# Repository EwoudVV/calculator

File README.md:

# Calculator

a calculator built from logic chips. there is no microcontroller or firmware.

it takes whole numbers from 0 to 9999 and does addition, subtraction, multiplication and division. it shows negative results, rounds division to two decimal places, and has lights for overflow, divide by zero and a full input.

three registers hold the numbers. a shared decimal adder works through them one digit at a time. the controller runs the loops for multiplication and long division.

## calculation times

calculated at a 96 kHz clock.

| calculation | clock cycles | time |
| --- | ---: | ---: |
| 27 + 15 or 27 − 15 | 43 | 0.45 ms |
| 12 × 34 | 369 | 3.84 ms |
| 99 × 99 | 2,253 | 23.47 ms |
| 7 ÷ 2 | 373 | 3.89 ms |
| 9999 ÷ 1 | 709 | 7.39 ms |

## pcb

the board is 140 × 120 mm. the keypad and display are on the front, with surface mount logic on both sides. it runs on 5 V.

open [calculator.kicad_pro](calculator.kicad_pro) in KiCad 10. the [build notes](BUILD.md) have the board status and parts list. progress from the breadboard design is in [JOURNAL.md](JOURNAL.md).

made for Hack Club Half Life, week 5

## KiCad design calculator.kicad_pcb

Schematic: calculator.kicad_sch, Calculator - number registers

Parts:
C101, C102, C103, C104, C105, C106, C107, C108, C109, C110, C111, C112, C113, C114, C115, C121, C122: 100n; C_0603_1608Metric
J101: 5V / GND; PinHeader_1x02_P2.54mm_Vertical
U101, U102, U103, U104, U105, U106, U107, U108, U109, U110, U111, U112: CD74HC299M96; SOIC-20W_7.5x12.8mm_P1.27mm
U113, U114, U115: CD74HC157M96; SOIC-16_3.9x9.9mm_P1.27mm
U121, U122: CD74HC153M96; SOIC-16_3.9x9.9mm_P1.27mm

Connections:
+5V: C101.1, C102.1, C103.1, C104.1, C105.1, C106.1, C107.1, C108.1, C109.1, C110.1, C111.1, C112.1, C113.1, C114.1, C115.1, C121.1, C122.1, J101.1, U101.20 (VCC), U102.20 (VCC), U103.20 (VCC), U104.20 (VCC), U105.20 (VCC), U106.20 (VCC), U107.20 (VCC), U108.20 (VCC), U109.20 (VCC), U110.20 (VCC), U111.20 (VCC), U112.20 (VCC), U113.16 (VCC), U114.16 (VCC), U115.16 (VCC), U121.16 (VCC), U122.16 (VCC); also elsewhere on the board
/ALU_DIGIT_0: U113.3 (I1a), U114.3 (I1a), U115.3 (I1a); also elsewhere on the board
/ALU_DIGIT_1: U113.6 (I1b), U114.6 (I1b), U115.6 (I1b); also elsewhere on the board
/ALU_DIGIT_2: U113.10 (I1c), U114.10 (I1c), U115.10 (I1c); also elsewhere on the board
/ALU_DIGIT_3: U113.13 (I1d), U114.13 (I1d), U115.13 (I1d); also elsewhere on the board
/A_SERIAL_RIGHT_0: U101.11 (Ds0), U113.4 (Za)
/A_SERIAL_RIGHT_1: U102.11 (Ds0), U113.7 (Zb)
/A_SERIAL_RIGHT_2: U103.11 (Ds0), U113.9 (Zc)
/A_SERIAL_RIGHT_3: U104.11 (Ds0), U113.12 (Zd)
/A_TOP_0: U101.8 (Q0), U121.3 (I3a)
/A_TOP_1: U102.8 (Q0), U121.13 (I3b)
/A_TOP_2: U103.8 (Q0), U122.3 (I3a)
/A_TOP_3: U104.8 (Q0), U122.13 (I3b)
/A_UNITS_0: U101.17 (Q7), U113.2 (I0a); also elsewhere on the board
/A_UNITS_1: U102.17 (Q7), U113.5 (I0b); also elsewhere on the board
/A_UNITS_2: U103.17 (Q7), U113.11 (I0c); also elsewhere on the board
/A_UNITS_3: U104.17 (Q7), U113.14 (I0d); also elsewhere on the board
/BANK_RESET_N: U101.9 (Mr), U102.9 (Mr), U103.9 (Mr), U104.9 (Mr), U105.9 (Mr), U106.9 (Mr), U107.9 (Mr), U108.9 (Mr), U109.9 (Mr), U110.9 (Mr), U111.9 (Mr), U112.9 (Mr); also elsewhere on the board
/B_SERIAL_RIGHT_0: U105.11 (Ds0), U114.4 (Za)
/B_SERIAL_RIGHT_1: U106.11 (Ds0), U114.7 (Zb)
/B_SERIAL_RIGHT_2: U107.11 (Ds0), U114.9 (Zc)
/B_SERIAL_RIGHT_3: U108.11 (Ds0), U114.12 (Zd)
/B_TOP_0: U105.8 (Q0)
/B_TOP_1: U106.8 (Q0)
/B_TOP_2: U107.8 (Q0)
/B_TOP_3: U108.8 (Q0)
/B_UNITS_0: U105.17 (Q7), U114.2 (I0a); also elsewhere on the board
/B_UNITS_1: U106.17 (Q7), U114.5 (I0b); also elsewhere on the board
/B_UNITS_2: U107.17 (Q7), U114.11 (I0c); also elsewhere on the board
/B_UNITS_3: U108.17 (Q7), U114.14 (I0d); also elsewhere on the board
/LEFT_LOAD_0: U101.18 (Ds7), U105.18 (Ds7), U109.18 (Ds7), U121.7 (Za)
/LEFT_LOAD_1: U102.18 (Ds7), U106.18 (Ds7), U110.18 (Ds7), U121.9 (Zb)
/LEFT_LOAD_2: U103.18 (Ds7), U107.18 (Ds7), U111.18 (Ds7), U122.7 (Za)
/LEFT_LOAD_3: U104.18 (Ds7), U108.18 (Ds7), U112.18 (Ds7), U122.9 (Zb)
/W_SERIAL_RIGHT_0: U109.11 (Ds0), U115.4 (Za)
/W_SERIAL_RIGHT_1: U110.11 (Ds0), U115.7 (Zb)
/W_SERIAL_RIGHT_2: U111.11 (Ds0), U115.9 (Zc)
/W_SERIAL_RIGHT_3: U112.11 (Ds0), U115.12 (Zd)
/W_TOP_0: U109.8 (Q0)
/W_TOP_1: U110.8 (Q0)
/W_TOP_2: U111.8 (Q0)
/W_TOP_3: U112.8 (Q0)
/W_UNITS_0: U109.17 (Q7), U115.2 (I0a); also elsewhere on the board
/W_UNITS_1: U110.17 (Q7), U115.5 (I0b); also elsewhere on the board
/W_UNITS_2: U111.17 (Q7), U115.11 (I0c); also elsewhere on the board
/W_UNITS_3: U112.17 (Q7), U115.14 (I0d); also elsewhere on the board
A_ROTATE_RIGHT: U101.1 (S0), U102.1 (S0), U103.1 (S0), U104.1 (S0); also elsewhere on the board
A_SHIFT_LEFT: U101.19 (S1), U102.19 (S1), U103.19 (S1), U104.19 (S1); also elsewhere on the board
A_WRITE_ALU: U113.1 (S); also elsewhere on the board
BANK_CLK: U101.12 (Cp), U102.12 (Cp), U103.12 (Cp), U104.12 (Cp), U105.12 (Cp), U106.12 (Cp), U107.12 (Cp), U108.12 (Cp), U109.12 (Cp), U110.12 (Cp), U111.12 (Cp), U112.12 (Cp); also elsewhere on the board
B_ROTATE_RIGHT: U105.1 (S0), U106.1 (S0), U107.1 (S0), U108.1 (S0); also elsewhere on the board
B_SHIFT_LEFT: U105.19 (S1), U106.19 (S1), U107.19 (S1), U108.19 (S1); also elsewhere on the board
B_WRITE_ALU: U114.1 (S); also elsewhere on the board
GND: C101.2, C102.2, C103.2, C104.2, C105.2, C106.2, C107.2, C108.2, C109.2, C110.2, C111.2, C112.2, C113.2, C114.2, C115.2, C121.2, C122.2, J101.2, U101.2 (OE1), U101.3 (OE2), U101.10 (GND), U102.2 (OE1), U102.3 (OE2), U102.10 (GND), U103.2 (OE1), U103.3 (OE2), U103.10 (GND), U104.2 (OE1), U104.3 (OE2), U104.10 (GND), U105.2 (OE1), U105.3 (OE2), U105.10 (GND), U106.2 (OE1), U106.3 (OE2), U106.10 (GND), U107.2 (OE1), U107.3 (OE2), U107.10 (GND), U108.2 (OE1), U108.3 (OE2), U108.10 (GND), U109.2 (OE1), U109.3 (OE2), U109.10 (GND), U110.2 (OE1), U110.3 (OE2), U110.10 (GND), U111.2 (OE1), U111.3 (OE2), U111.10 (GND), U112.2 (OE1), U112.3 (OE2), U112.10 (GND), U113.8 (GND), U113.15 (E), U114.8 (GND), U114.15 (E), U115.8 (GND), U115.15 (E), U121.1 (Ea), U121.6 (I0a), U121.8 (GND), U121.10 (I0b), U121.15 (Eb), U122.1 (Ea), U122.6 (I0a), U122.8 (GND), U122.10 (I0b), U122.15 (Eb); also elsewhere on the board
KEY_DIGIT_0: U121.5 (I1a); also elsewhere on the board
KEY_DIGIT_1: U121.11 (I1b); also elsewhere on the board
KEY_DIGIT_2: U122.5 (I1a); also elsewhere on the board
KEY_DIGIT_3: U122.11 (I1b); also elsewhere on the board
LEFT_SELECT_0: U121.14 (S0), U122.14 (S0); also elsewhere on the board
LEFT_SELECT_1: U121.2 (S1), U122.2 (S1); also elsewhere on the board
QUOTIENT_DIGIT_0: U121.4 (I2a); also elsewhere on the board
QUOTIENT_DIGIT_1: U121.12 (I2b); also elsewhere on the board
QUOTIENT_DIGIT_2: U122.4 (I2a); also elsewhere on the board
QUOTIENT_DIGIT_3: U122.12 (I2b); also elsewhere on the board
W_ROTATE_RIGHT: U109.1 (S0), U110.1 (S0), U111.1 (S0), U112.1 (S0); also elsewhere on the board
W_SHIFT_LEFT: U109.19 (S1), U110.19 (S1), U111.19 (S1), U112.19 (S1); also elsewhere on the board
W_WRITE_ALU: U115.1 (S); also elsewhere on the board

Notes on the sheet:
A: first number
BCD bit 0
BCD bit 1
BCD bit 2
BCD bit 3
B: second number
W: working/result number
Shared digit for a left shift
Number registers. Shared arithmetic is on sheet 2.
S0,S1: 00 hold / 10 arithmetic rotate / 01 append a digit.
Unused parallel ports are outputs with OE1/OE2 LOW; no external load.
Parallel-load mode 11 must never be selected.

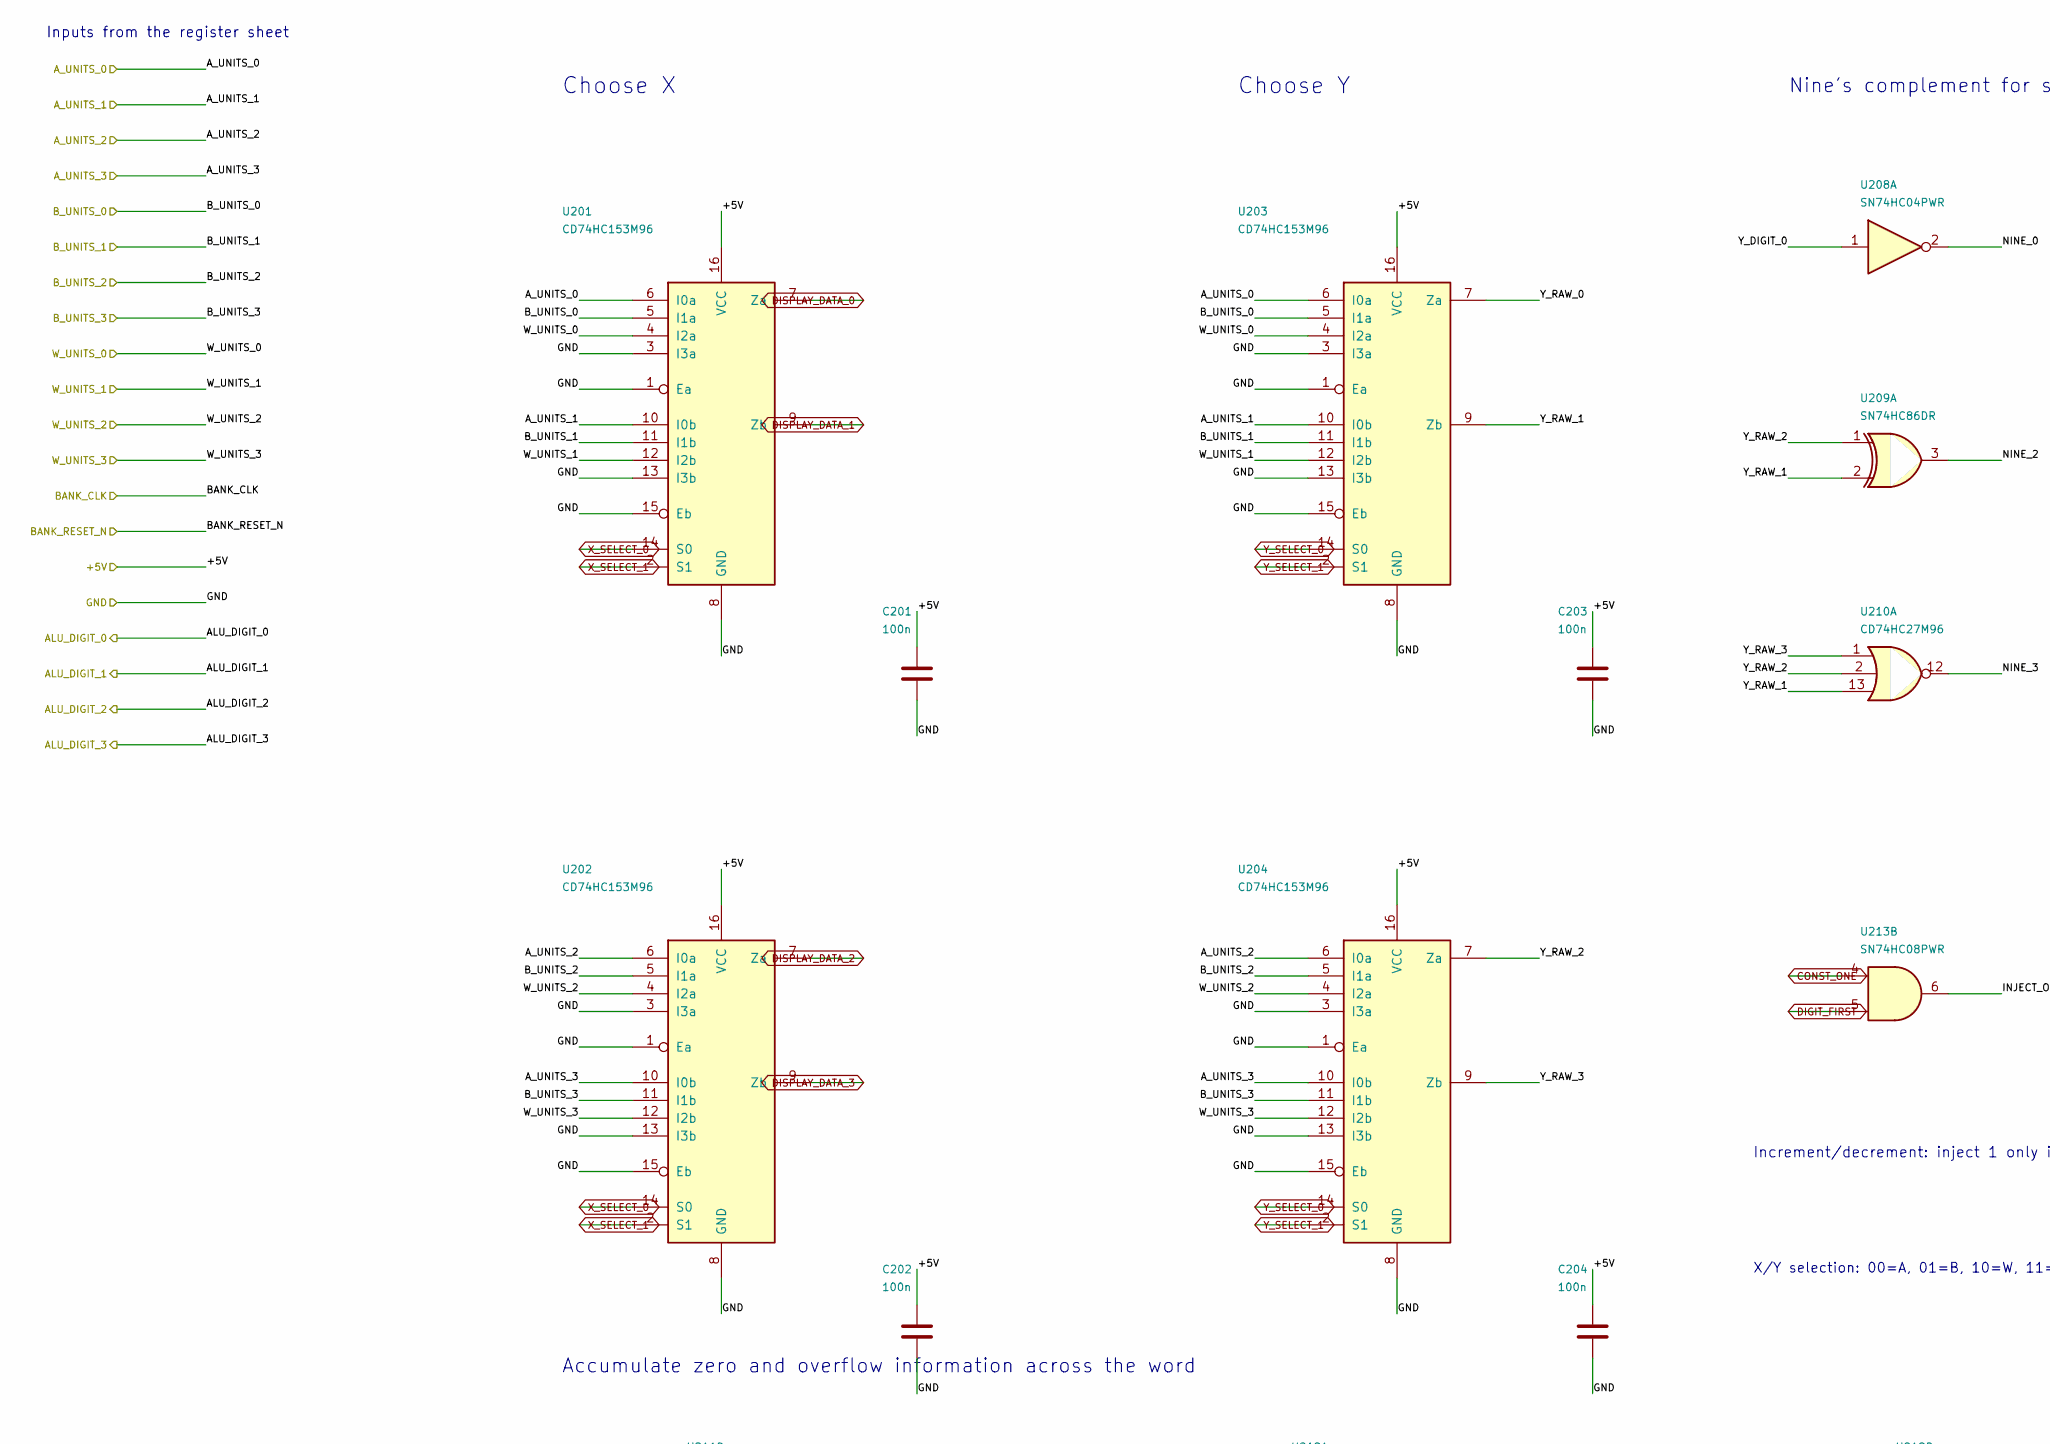
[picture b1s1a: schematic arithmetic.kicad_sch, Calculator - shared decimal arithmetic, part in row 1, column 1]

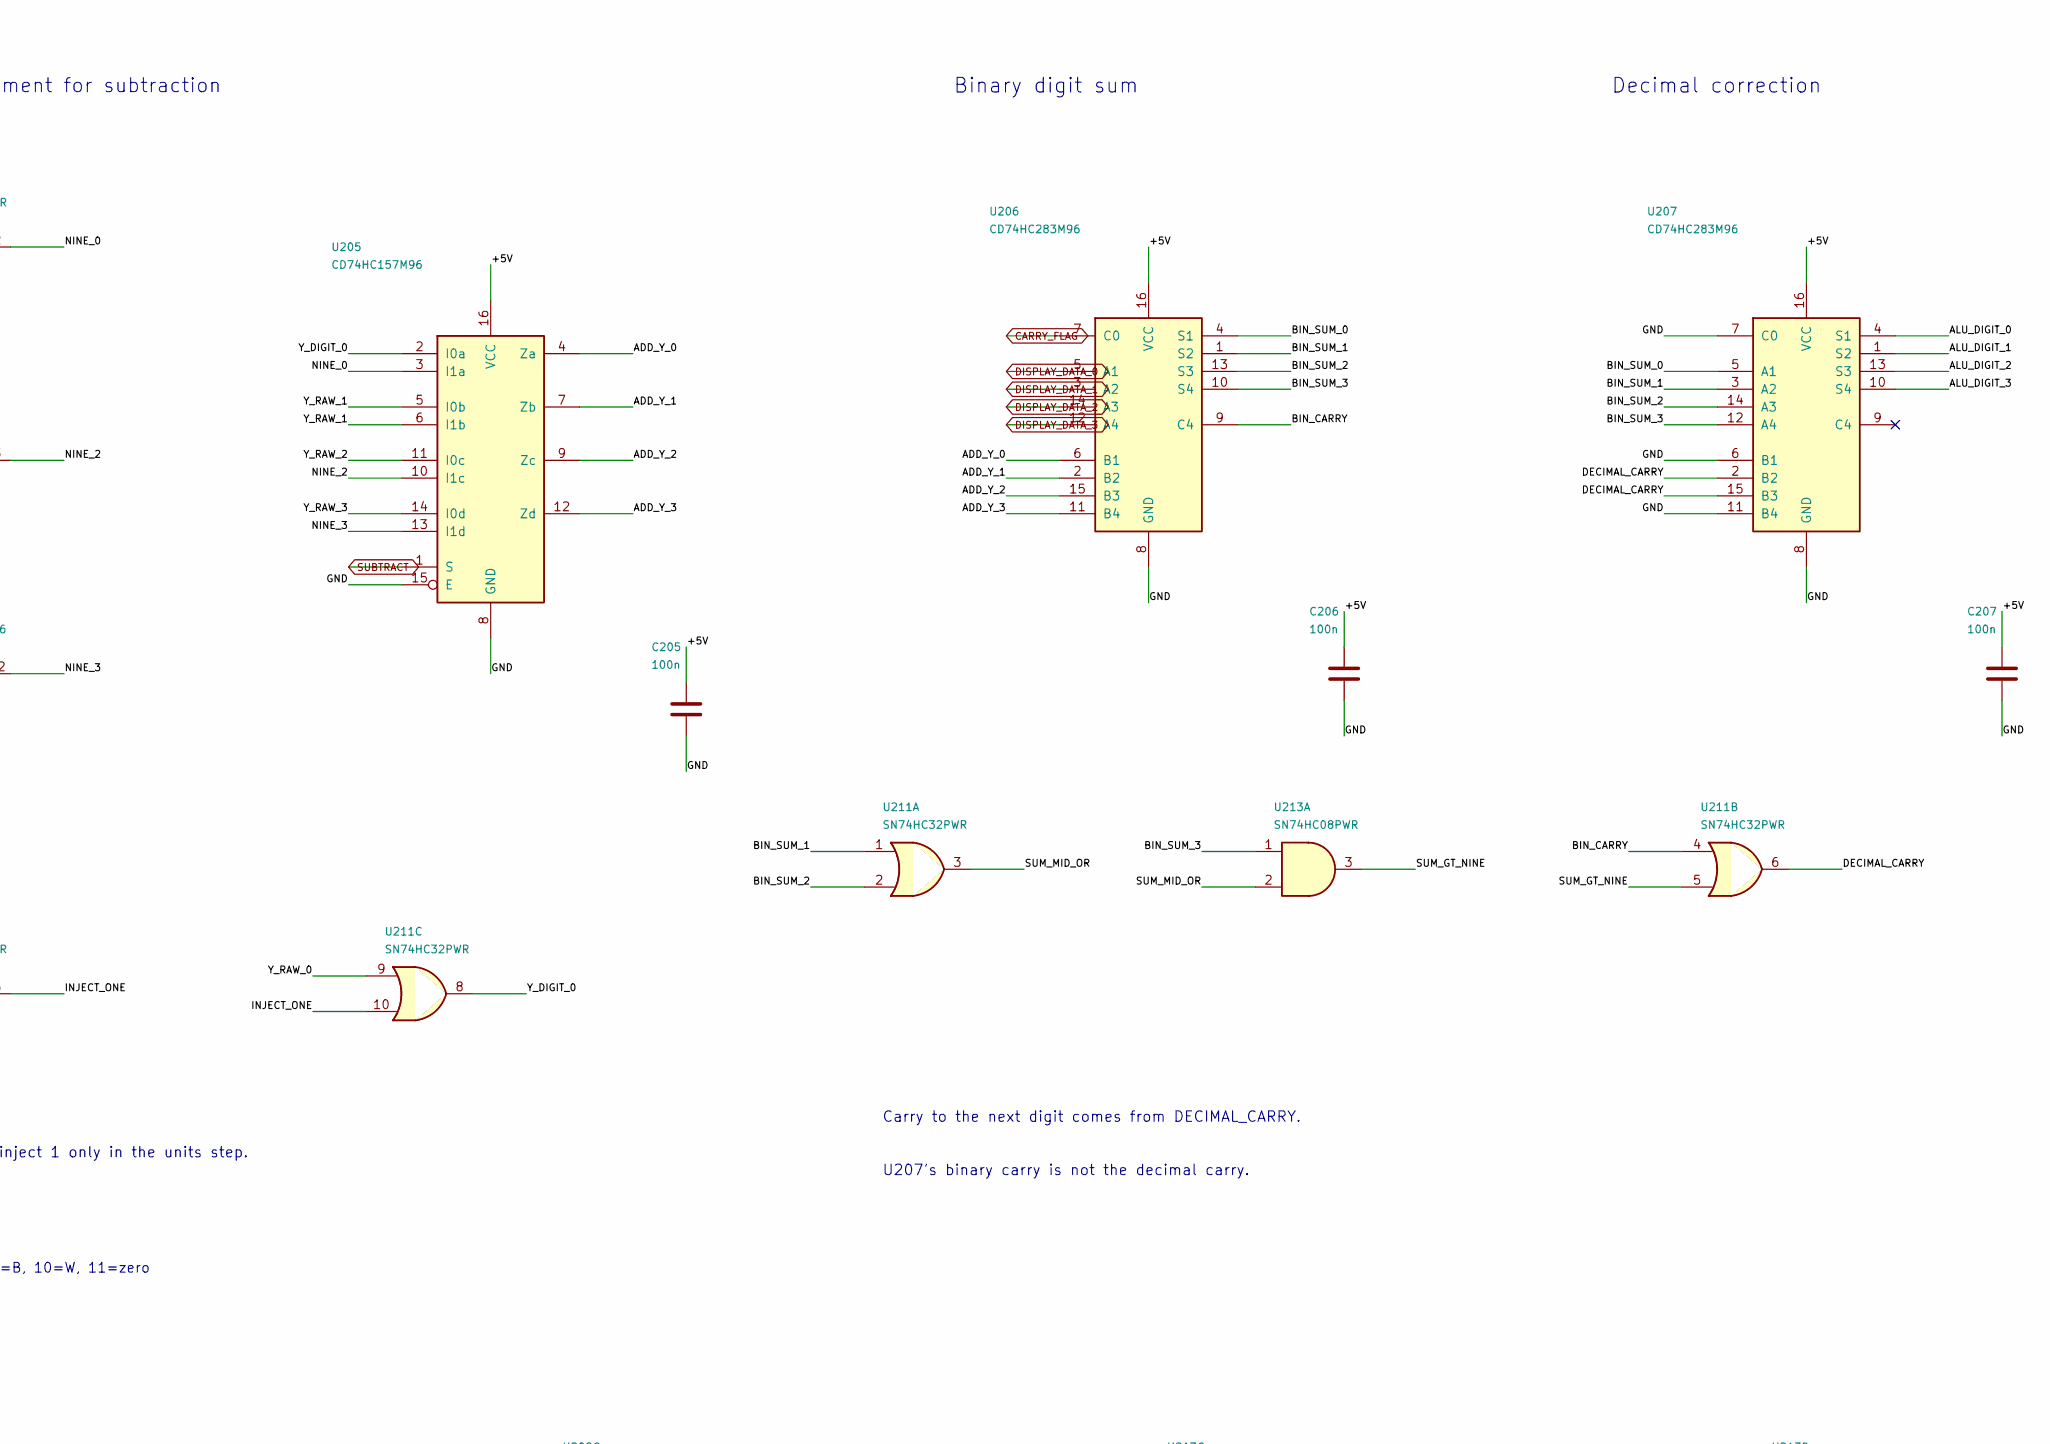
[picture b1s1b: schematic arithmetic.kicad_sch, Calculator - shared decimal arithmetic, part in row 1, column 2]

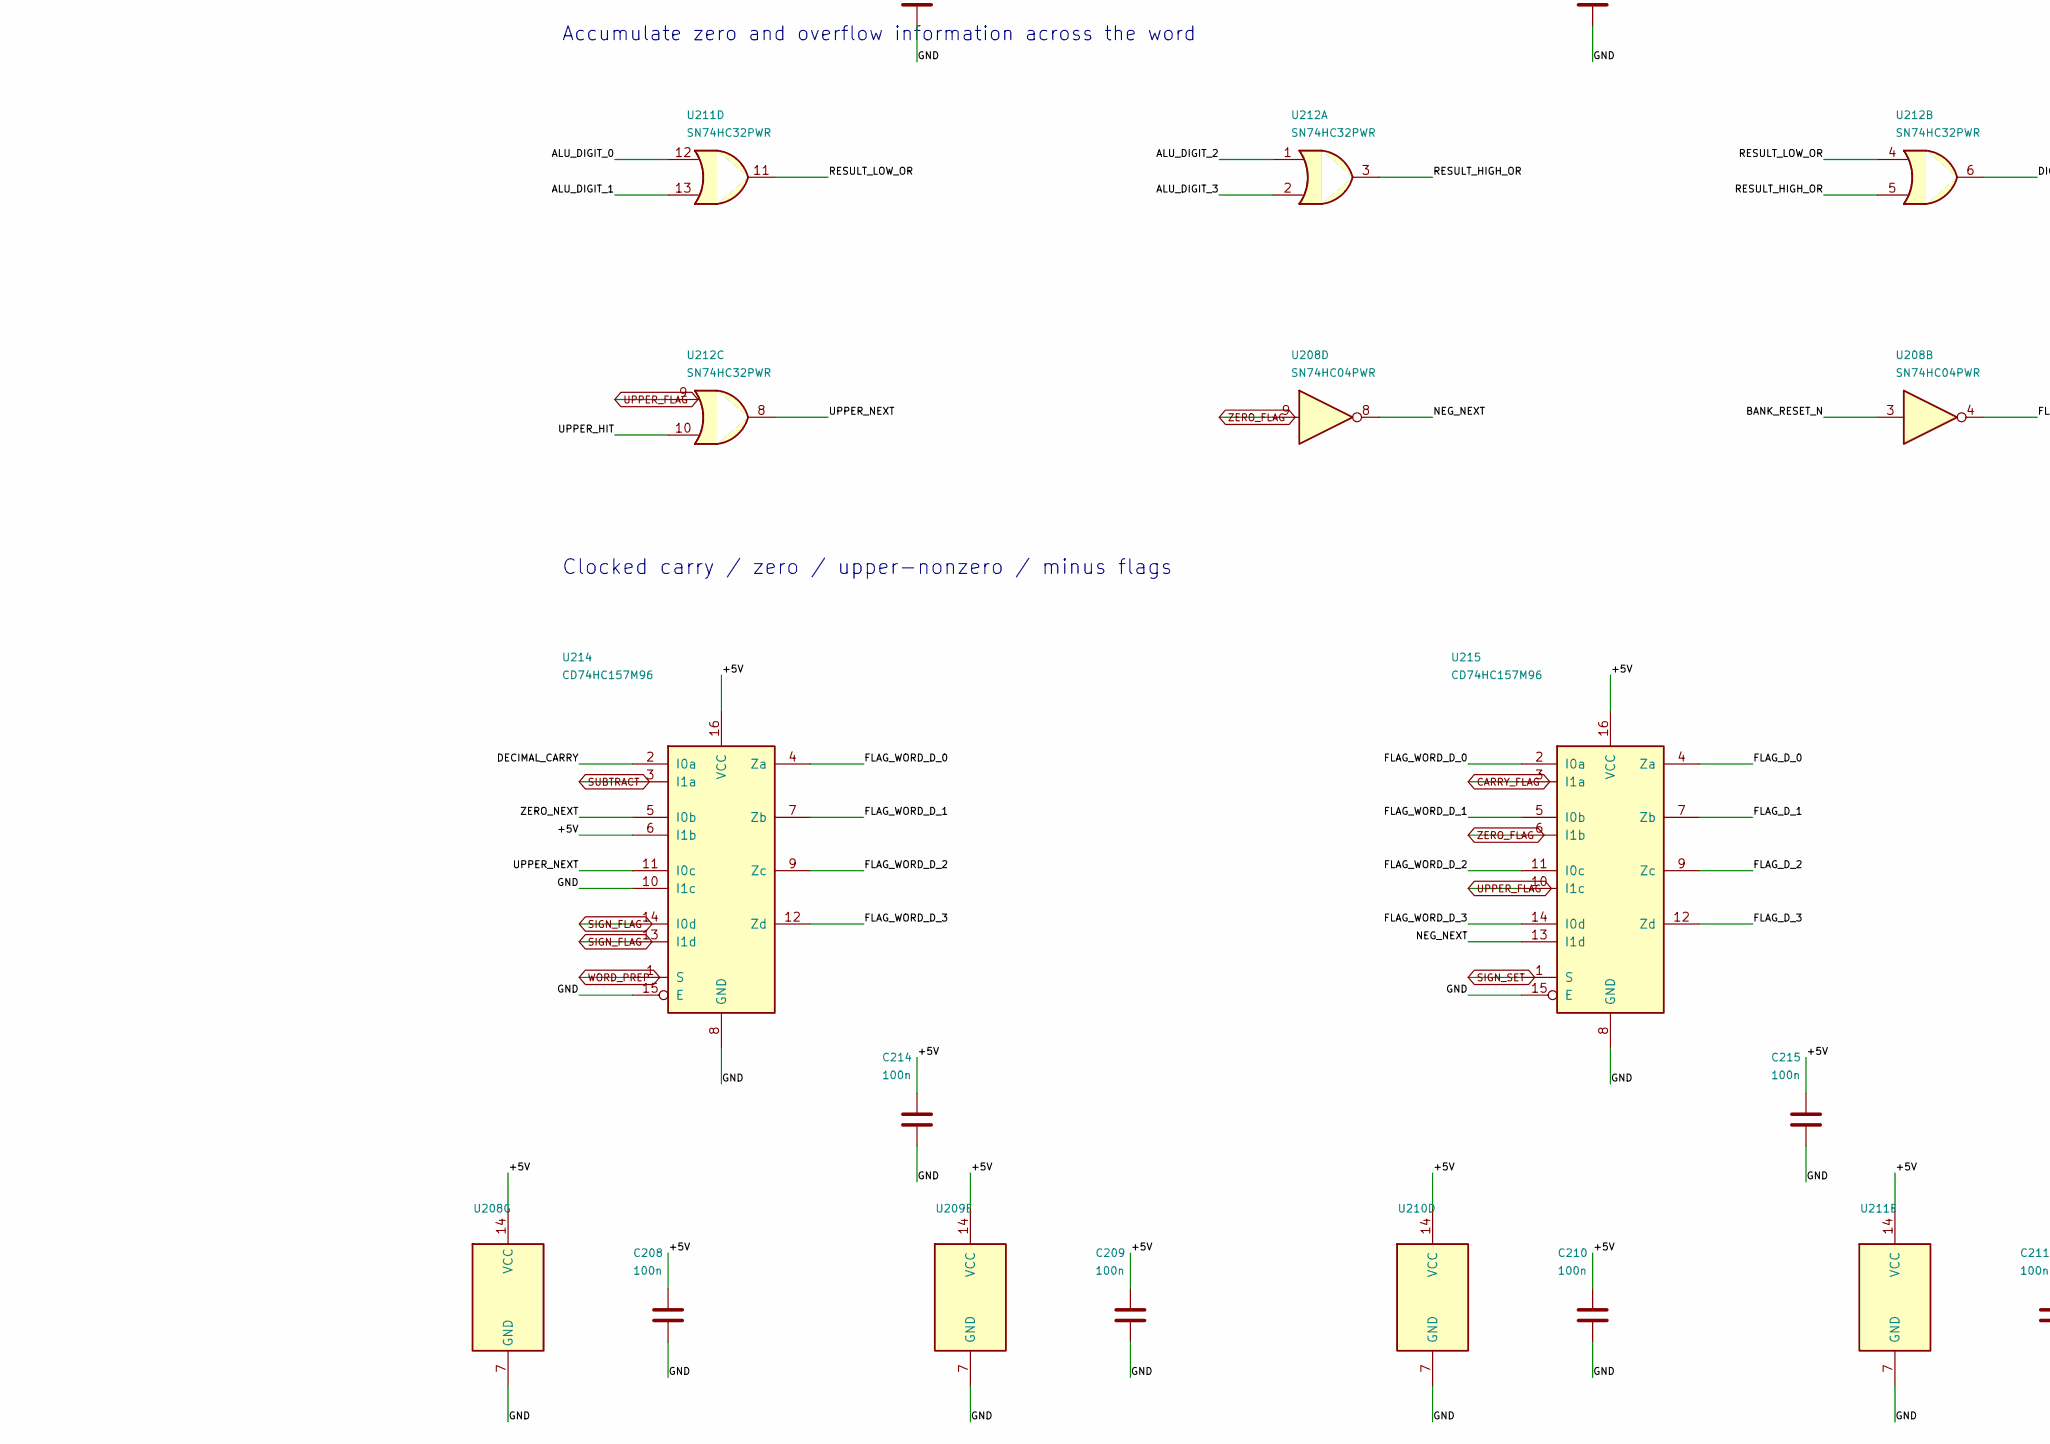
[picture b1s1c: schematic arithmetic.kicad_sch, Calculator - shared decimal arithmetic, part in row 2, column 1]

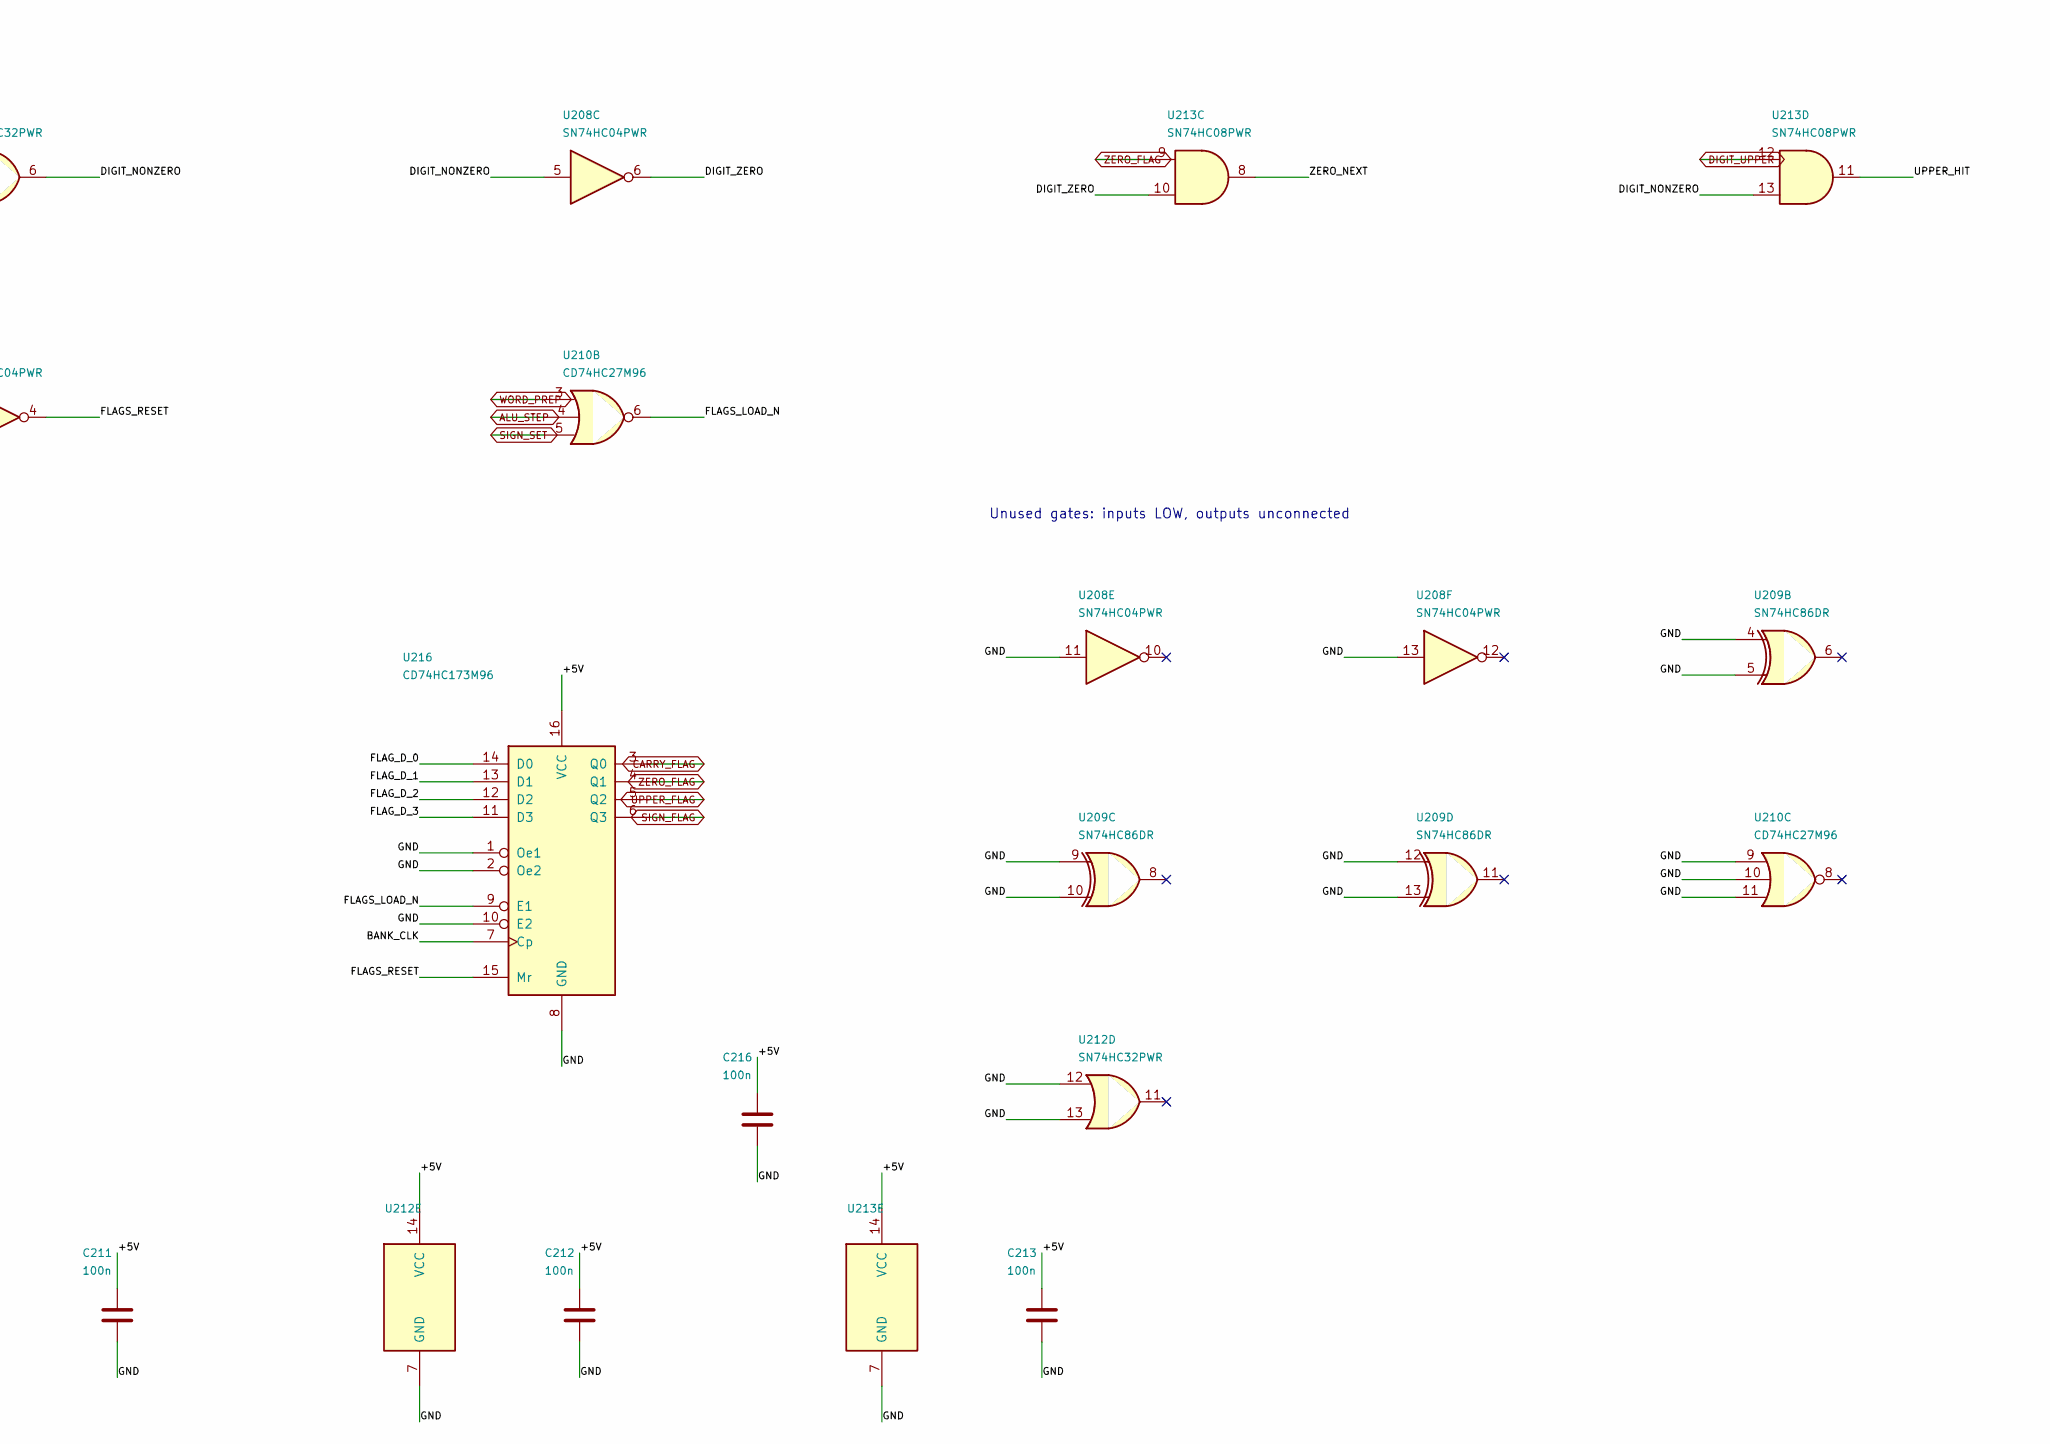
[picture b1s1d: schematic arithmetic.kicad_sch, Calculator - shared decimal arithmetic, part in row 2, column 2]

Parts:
C201, C202, C203, C204, C205, C206, C207, C208, C209, C210, C211, C212, C213, C214, C215, C216: 100n; C_0603_1608Metric
U201, U202, U203, U204: CD74HC153M96; SOIC-16_3.9x9.9mm_P1.27mm
U205, U214, U215: CD74HC157M96; SOIC-16_3.9x9.9mm_P1.27mm
U206, U207: CD74HC283M96; SOIC-16_3.9x9.9mm_P1.27mm
U208: SN74HC04PWR; TSSOP-14_4.4x5mm_P0.65mm
U209: SN74HC86DR; SOIC-14_3.9x8.7mm_P1.27mm
U210: CD74HC27M96; SOIC-14_3.9x8.7mm_P1.27mm
U211, U212: SN74HC32PWR; TSSOP-14_4.4x5mm_P0.65mm
U213: SN74HC08PWR; TSSOP-14_4.4x5mm_P0.65mm
U216: CD74HC173M96; SOIC-16_3.9x9.9mm_P1.27mm

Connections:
+5V: C201.1, C202.1, C203.1, C204.1, C205.1, C206.1, C207.1, C208.1, C209.1, C210.1, C211.1, C212.1, C213.1, C214.1, C215.1, C216.1, U201.16 (VCC), U202.16 (VCC), U203.16 (VCC), U204.16 (VCC), U205.16 (VCC), U206.16 (VCC), U207.16 (VCC), U208.14 (VCC), U209.14 (VCC), U210.14 (VCC), U211.14 (VCC), U212.14 (VCC), U213.14 (VCC), U214.6 (I1b), U214.16 (VCC), U215.16 (VCC), U216.16 (VCC); also elsewhere on the board
/ALU_DIGIT_0: U207.4 (S1), U211.12; also elsewhere on the board
/ALU_DIGIT_1: U207.1 (S2), U211.13; also elsewhere on the board
/ALU_DIGIT_2: U207.13 (S3), U212.1; also elsewhere on the board
/ALU_DIGIT_3: U207.10 (S4), U212.2; also elsewhere on the board
/A_UNITS_0: U201.6 (I0a), U203.6 (I0a); also elsewhere on the board
/A_UNITS_1: U201.10 (I0b), U203.10 (I0b); also elsewhere on the board
/A_UNITS_2: U202.6 (I0a), U204.6 (I0a); also elsewhere on the board
/A_UNITS_3: U202.10 (I0b), U204.10 (I0b); also elsewhere on the board
/Arithmetic/ADD_Y_0: U205.4 (Za), U206.6 (B1)
/Arithmetic/ADD_Y_1: U205.7 (Zb), U206.2 (B2)
/Arithmetic/ADD_Y_2: U205.9 (Zc), U206.15 (B3)
/Arithmetic/ADD_Y_3: U205.12 (Zd), U206.11 (B4)
/Arithmetic/BIN_CARRY: U206.9 (C4), U211.4
/Arithmetic/BIN_SUM_0: U206.4 (S1), U207.5 (A1)
/Arithmetic/BIN_SUM_1: U206.1 (S2), U207.3 (A2), U211.1
/Arithmetic/BIN_SUM_2: U206.13 (S3), U207.14 (A3), U211.2
/Arithmetic/BIN_SUM_3: U206.10 (S4), U207.12 (A4), U213.1
/Arithmetic/DECIMAL_CARRY: U207.2 (B2), U207.15 (B3), U211.6, U214.2 (I0a)
/Arithmetic/DIGIT_NONZERO: U208.5, U212.6, U213.13
/Arithmetic/DIGIT_ZERO: U208.6, U213.10
/Arithmetic/FLAGS_LOAD_N: U210.6, U216.9 (E1)
/Arithmetic/FLAGS_RESET: U208.4, U216.15 (Mr)
/Arithmetic/FLAG_D_0: U215.4 (Za), U216.14 (D0)
/Arithmetic/FLAG_D_1: U215.7 (Zb), U216.13 (D1)
/Arithmetic/FLAG_D_2: U215.9 (Zc), U216.12 (D2)
/Arithmetic/FLAG_D_3: U215.12 (Zd), U216.11 (D3)
/Arithmetic/FLAG_WORD_D_0: U214.4 (Za), U215.2 (I0a)
/Arithmetic/FLAG_WORD_D_1: U214.7 (Zb), U215.5 (I0b)
/Arithmetic/FLAG_WORD_D_2: U214.9 (Zc), U215.11 (I0c)
/Arithmetic/FLAG_WORD_D_3: U214.12 (Zd), U215.14 (I0d)
/Arithmetic/INJECT_ONE: U211.10, U213.6
/Arithmetic/NEG_NEXT: U208.8, U215.13 (I1d)
/Arithmetic/NINE_0: U205.3 (I1a), U208.2
/Arithmetic/NINE_2: U205.10 (I1c), U209.3
/Arithmetic/NINE_3: U205.13 (I1d), U210.12
/Arithmetic/RESULT_HIGH_OR: U212.3, U212.5
/Arithmetic/RESULT_LOW_OR: U211.11, U212.4
/Arithmetic/SUM_GT_NINE: U211.5, U213.3
/Arithmetic/SUM_MID_OR: U211.3, U213.2
/Arithmetic/UPPER_HIT: U212.10, U213.11
/Arithmetic/UPPER_NEXT: U212.8, U214.11 (I0c)
/Arithmetic/Y_DIGIT_0: U205.2 (I0a), U208.1, U211.8
/Arithmetic/Y_RAW_0: U203.7 (Za), U211.9
/Arithmetic/Y_RAW_1: U203.9 (Zb), U205.5 (I0b), U205.6 (I1b), U209.2, U210.13
/Arithmetic/Y_RAW_2: U204.7 (Za), U205.11 (I0c), U209.1, U210.2
/Arithmetic/Y_RAW_3: U204.9 (Zb), U205.14 (I0d), U210.1
/Arithmetic/ZERO_NEXT: U213.8, U214.5 (I0b)
/BANK_RESET_N: U208.3; also elsewhere on the board
/B_UNITS_0: U201.5 (I1a), U203.5 (I1a); also elsewhere on the board
/B_UNITS_1: U201.11 (I1b), U203.11 (I1b); also elsewhere on the board
/B_UNITS_2: U202.5 (I1a), U204.5 (I1a); also elsewhere on the board
/B_UNITS_3: U202.11 (I1b), U204.11 (I1b); also elsewhere on the board
/W_UNITS_0: U201.4 (I2a), U203.4 (I2a); also elsewhere on the board
/W_UNITS_1: U201.12 (I2b), U203.12 (I2b); also elsewhere on the board
/W_UNITS_2: U202.4 (I2a), U204.4 (I2a); also elsewhere on the board
/W_UNITS_3: U202.12 (I2b), U204.12 (I2b); also elsewhere on the board
ALU_STEP: U210.4; also elsewhere on the board
BANK_CLK: U216.7 (Cp); also elsewhere on the board
CARRY_FLAG: U206.7 (C0), U215.3 (I1a), U216.3 (Q0); also elsewhere on the board
CONST_ONE: U213.4; also elsewhere on the board
DIGIT_FIRST: U213.5; also elsewhere on the board
DIGIT_UPPER: U213.12; also elsewhere on the board
DISPLAY_DATA_0: U201.7 (Za), U206.5 (A1); also elsewhere on the board
DISPLAY_DATA_1: U201.9 (Zb), U206.3 (A2); also elsewhere on the board
DISPLAY_DATA_2: U202.7 (Za), U206.14 (A3); also elsewhere on the board
DISPLAY_DATA_3: U202.9 (Zb), U206.12 (A4); also elsewhere on the board
GND: C201.2, C202.2, C203.2, C204.2, C205.2, C206.2, C207.2, C208.2, C209.2, C210.2, C211.2, C212.2, C213.2, C214.2, C215.2, C216.2, U201.1 (Ea), U201.3 (I3a), U201.8 (GND), U201.13 (I3b), U201.15 (Eb), U202.1 (Ea), U202.3 (I3a), U202.8 (GND), U202.13 (I3b), U202.15 (Eb), U203.1 (Ea), U203.3 (I3a), U203.8 (GND), U203.13 (I3b), U203.15 (Eb), U204.1 (Ea), U204.3 (I3a), U204.8 (GND), U204.13 (I3b), U204.15 (Eb), U205.8 (GND), U205.15 (E), U206.8 (GND), U207.6 (B1), U207.7 (C0), U207.8 (GND), U207.11 (B4), U208.7 (GND), U208.11, U208.13, U209.4, U209.5, U209.7 (GND), U209.9, U209.10, U209.12, U209.13, U210.7 (GND), U210.9, U210.10, U210.11, U211.7 (GND), U212.7 (GND), U212.12, U212.13, U213.7 (GND), U214.8 (GND), U214.10 (I1c), U214.15 (E), U215.8 (GND), U215.15 (E), U216.1 (Oe1), U216.2 (Oe2), U216.8 (GND), U216.10 (E2); also elsewhere on the board
SIGN_FLAG: U214.13 (I1d), U214.14 (I0d), U216.6 (Q3); also elsewhere on the board
SIGN_SET: U210.5, U215.1 (S); also elsewhere on the board
SUBTRACT: U205.1 (S), U214.3 (I1a); also elsewhere on the board
UPPER_FLAG: U212.9, U215.10 (I1c), U216.5 (Q2); also elsewhere on the board
WORD_PREP: U210.3, U214.1 (S); also elsewhere on the board
X_SELECT_0: U201.14 (S0), U202.14 (S0); also elsewhere on the board
X_SELECT_1: U201.2 (S1), U202.2 (S1); also elsewhere on the board
Y_SELECT_0: U203.14 (S0), U204.14 (S0); also elsewhere on the board
Y_SELECT_1: U203.2 (S1), U204.2 (S1); also elsewhere on the board
ZERO_FLAG: U208.9, U213.9, U215.6 (I1b), U216.4 (Q1); also elsewhere on the board

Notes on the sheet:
Inputs from the register sheet
Choose X
Choose Y
X/Y selection: 00=A, 01=B, 10=W, 11=zero
Nine's complement for subtraction
Increment/decrement: inject 1 only in the units step.
Binary digit sum
Decimal correction
Carry to the next digit comes from DECIMAL_CARRY.
U207's binary carry is not the decimal carry.
Accumulate zero and overflow information across the word
Clocked carry / zero / upper-nonzero / minus flags
Unused gates: inputs LOW, outputs unconnected
